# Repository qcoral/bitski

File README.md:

# bitski

yup. it's the thing!

Inital sketch of what I am attempting to make:

Let's see how this works out

Feature list (planned):

- WiFi
- Bluetooth
- LiPo battery management
- High quality 6-axis IMU + 3 axis magnometer
- Pressure and altitude sensing
- Temperature & Humidity sensing
- 4 buttons?
- Power switch
- ??? by ??? 0603 LED matrix

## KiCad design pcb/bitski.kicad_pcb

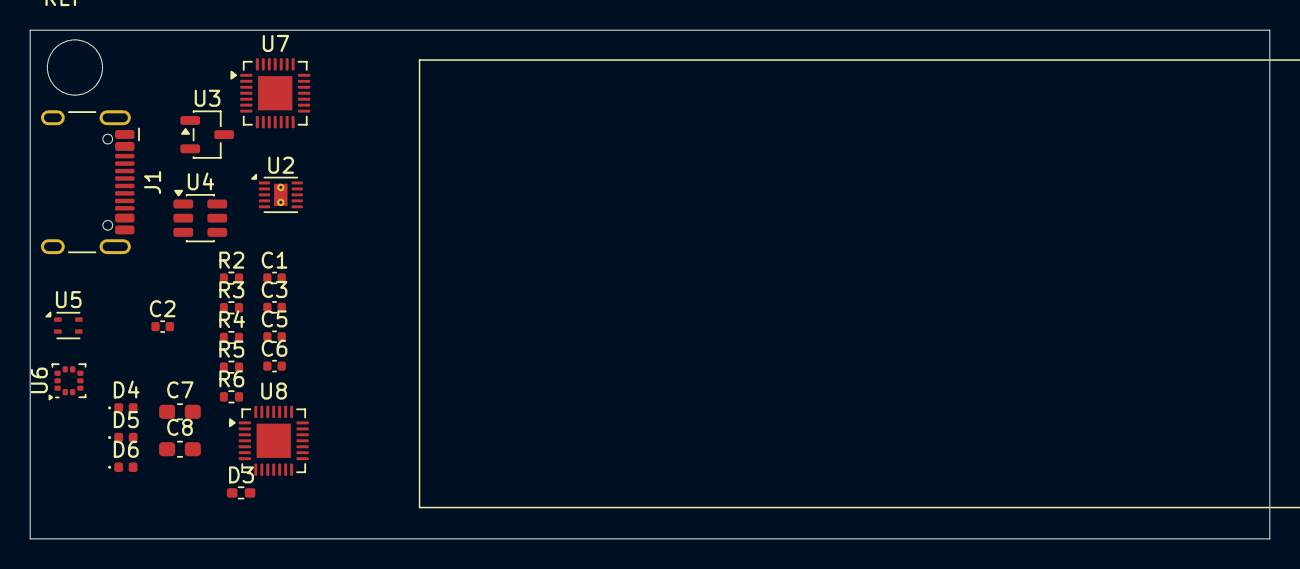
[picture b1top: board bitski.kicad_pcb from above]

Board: 2 copper layers, 83.1 x 34.1 mm, 25 parts (1 on the bottom side), 14 nets, no tracks yet.

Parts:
C1: 10uF; C_0402_1005Metric
C2: C_Small; C_0402_1005Metric
C3, C5, C6: 1uF; C_0402_1005Metric
C7, C8: 0pF; C_0603_1608Metric_Pad1.08x0.95mm_HandSolder
D3: LED_45deg; R_0402_1005Metric_Pad0.72x0.64mm_HandSolder
D4, D5, D6: LED_45deg; LED_0402_1005Metric
J1: Conn_02x12_Odd_Even; USB_C_Receptacle_HCTL_HC-TYPE-C-16P-01A
R2, R3: 5.1k; R_0402_1005Metric
R4: 10k; R_0402_1005Metric
R5, R6: 33; R_0402_1005Metric
U1: ESP32-S3-MINI-1-N8; ESP32-S2-MINI-1
U2: BQ25185; Texas_DLH0010A_WSON-10-1EP_2.2x2mm_P0.4mm_EP0.9x1.5mm_Therm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
U3: XC6206PxxxMR; SOT-23-3
U4: USBLC6-2SC6; SOT-23-6
U5: GXHT40AD; Sensirion_DFN-4_1.5x1.5mm_P0.8mm_SHT4x_NoCentralPad
U6: BMP580; ST_HLGA-10_2x2mm_P0.5mm_LayoutBorder3x2y
U7, U8: IS31FL3731-QF; QFN-28-1EP_4x4mm_P0.4mm_EP2.3x2.3mm

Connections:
+3V3: C2.1, U1.3 (3V3), U5.3 (VDD), U6.10 (VDD), U8.2 (VCC)
-BATT: C1.2, C2.2, C3.2, C5.2, C6.2, C7.2, C8.2, R2.2, R3.2, U1.1 (GND), U1.2 (GND), U1.42 (GND), U1.43 (GND), U1.46 (GND), U1.47 (GND), U1.48 (GND), U1.49 (GND), U1.50 (GND), U1.51 (GND), U1.52 (GND), U1.53 (GND), U1.54 (GND), U1.55 (GND), U1.56 (GND), U1.57 (GND), U1.58 (GND), U1.59 (GND), U1.60 (GND), U1.61 (GND), U1.62 (GND), U1.63 (GND), U1.64 (GND), U1.65 (GND), U2.5 (GND), U3.1 (GND), U4.2 (GND), U5.4 (VSS), U6.3 (VSS), U6.8 (VSS), U6.9 (VSS)
BATT_LOAD: C1.1, C5.1, U2.1 (SYS), U3.3 (VI)
unnamed: C3.1, R4.1
unnamed: C7.1, R6.1, U4.4 (I/O2)
unnamed: C8.1, R5.1, U4.6 (I/O1)
unnamed: C6.1, U3.2 (VO)
unnamed: R4.2, U1.45 (EN)
unnamed: U7.5 (GND), U7.29 (GND)
unnamed: U8.5 (GND), U8.29 (GND)
SHT40_SCL: U1.11 (IO7), U5.2 (SCL)
SHT40_SDA: U1.10 (IO6), U5.1 (SDA)
USB_DM_CLEAN: R5.2, U1.23 (USB_D-)
USB_DP_CLEAN: R6.2, U1.24 (USB_D+)

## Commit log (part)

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2026-03-06 started project
2026-03-09 updated schematic, added gitignore
2026-03-16 updated board waow
2026-03-17 more progress
2026-04-05 made changes waow
2026-04-28 waow updated board
2026-04-28 updates!
2026-04-29 holy
